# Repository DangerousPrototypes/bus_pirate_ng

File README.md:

# bus_pirate_ng
Bus Pirate NG firmware and hardware

Check the blog at http://dangerousprototypes.com/blog/2018/09/13/prototype-bus-pirate-next-gen-v1/<br><br>
---
### Building
- Install toolchain:
```
sudo apt-get update -y
sudo apt-get install -y gcc-arm-none-eabi
```
- Clone repository:
```
git clone --recursive https://github.com/DangerousPrototypes/bus_pirate_ng
cd bus_pirate_ng
```
- Compile modules in this order:
```
make -C libopencm3 lib/stm32/f1
make -C bootloader images
```
- Compile Bus Pirate:
```
make -C source images
```
- Output images:
```
bootloader/usbdfu.bin
source/buspirateNG.bin
```
<br>

---
### Bootloader
The firmware is compiled expecting a bootloader offset of 0x2000.<br>
The generated BusPirate image doesn't contain the bootloader, if your stm32 doesn't have it you must first flash:
```
bootloader/usbdfu.bin
```
Then enter DFU mode and flash:
```
source/buspirateNG.bin
```
### Bootloader-less
You can skip the bootloader entirely by modifying [`source/buspirateNG.ld`](source/buspirateNG.ld#L23),<br>
Replace:
```
ORIGIN = 0x08002000, LENGTH = 120K
```
With:
```
ORIGIN = 0x08000000, LENGTH = 128K
```
Now simply flash ```source/buspirateNG.bin``` into the stm32 using your favourite programmer.<br>

---
### Pinout
Pin functions are described at [`source/platform/beta2.h`](source/platform/beta2.h).
<br>

---
### Basic functionality using a BluePill
You can use this firmware in a simple Bluepill, skipping all the extra circuitry, but requires tweaking to ignore the PSU check.<br>
Edit ```initUI``` function at [`source/UI.c`](source/UI.c#L167) and change:
```
modeConfig.psu=0;
```
To:
```
modeConfig.psu=1;
```
Don't use PSU commands (w/W) after this modification!<br>
Keep in mind the bare STM32 can only talk 3.3V in push-pull mode and 5V in open-drain mode!<br>

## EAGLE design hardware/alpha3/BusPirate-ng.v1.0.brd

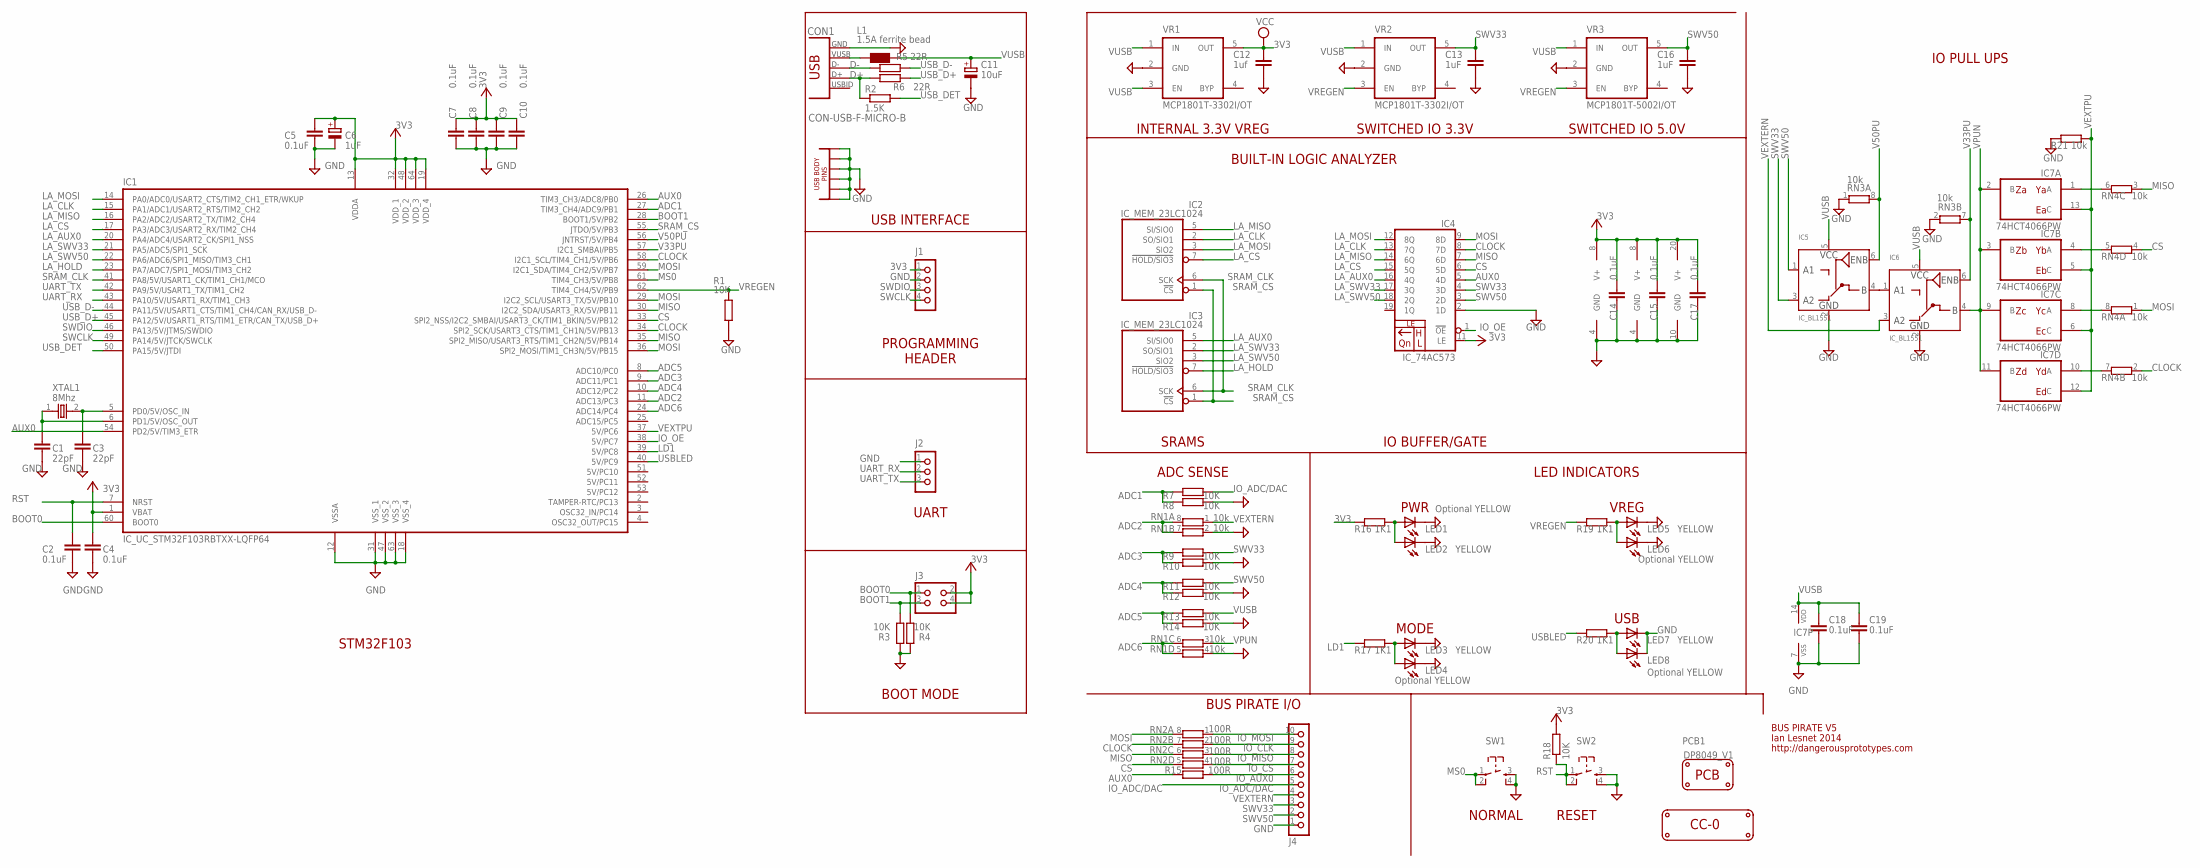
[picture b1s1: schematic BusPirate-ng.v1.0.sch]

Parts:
C1, C3: 22pF; C0603
C2, C4, C5, C7, C8, C9, C10, C14, C15, C17, C18, C19: 0.1uF; C0603
C6: 1uF; SMC_A
C11: 10uF; SMC_A
C12: 1uf; C0603
C13, C16: 1uF; C0603
CON1: CON-USB-F-MICRO-B; CON_USB_MICRO-B-1-MD05SMXXX-01
IC1: IC_UC_STM32F103RBTXX-LQFP64; LQFP64
IC2, IC3: IC_MEM_23LC1024; SOIC-8
IC4: IC_74AC573; TSSOP-20
IC5, IC6: IC_BL1551; SOT-363
IC7: 74HCT4066PW; 40XX_TSSOP14
J1: CON_HEADER_1X04; M1X4
J2: CON_HEADER_1X03-PTH; M1X3
J3: CON_HEADER_2X02-PTH; M2X2
J4: CON_HEADER_1X10-RIGHT_ANGLED_PTH_SHROUDED; M1X10_MALE_RIGHT_ANGLES_PTH_SHROUDED
L1: 1.5A ferrite bead; WE-KI_0805_B
LED1, LED4, LED6, LED8: Optional YELLOW; LED-805
LED2, LED3, LED5, LED7: YELLOW; LED-805
LOGO1: LOGO_CC-0
PCB1: PCB_DP_RECTANGLE-80X49; DP8049_V1
R1, R18: 10K; R603
R2: 1.5K; R603
R3, R4, R7, R8, R9, R10, R11, R12, R13, R14: 10K; R0603
R5, R6: 22R; R603
R15: 100R; R603
R16, R17, R19, R20: 1K1; R603
R21: 10k; R603
RN1, RN3, RN4: 10k; RN8P-4R-CRA06S
RN2: 100R; RN8P-4R-CRA06S
SW1, SW2: SW_TACT_4P; SW_TACT_SMALL
VR1, VR2: MCP1801T-3302I/OT; SOT-23-5@1
VR3: MCP1801T-5002I/OT; SOT-23-5@1
XTAL1: 8Mhz; XTAL_4X6

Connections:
3V3: C4.2, C5.2, C6.+, C7.2, C8.2, C9.2, C10.2, C12.1, C14.1, C15.1, C17.1, IC1.1 (VBAT), IC1.13 (VDDA), IC1.19 (VDD_4), IC1.32 (VDD_1), IC1.48 (VDD_2), IC1.64 (VDD_3), IC2.8 (V+), IC3.8 (V+), IC4.11 (LE), IC4.20 (V+), J1.1, J3.2, J3.4, R16.2, R18.2, VR1.5 (OUT)
ADC1: IC1.27 (TIM3_CH4/ADC9/PB1), R7.2, R8.2
ADC2: IC1.11 (ADC13/PC3), RN1.7 (2), RN1.8 (2)
ADC3: IC1.9 (ADC11/PC1), R9.2, R10.2
ADC4: IC1.10 (ADC12/PC2), R11.2, R12.2
ADC5: IC1.8 (ADC10/PC0), R13.2, R14.2
ADC6: IC1.24 (ADC14/PC4), RN1.5 (2), RN1.6 (2)
AUX0: IC1.26 (TIM3_CH3/ADC8/PB0), IC1.54 (PD2/5V/TIM3_ETR), IC4.5 (4D), R15.1
BOOT0: IC1.60 (BOOT0), J3.1, R4.1
BOOT1: IC1.28 (BOOT1/5V/PB2), J3.3, R3.1
CLOCK: IC1.34 (SPI2_SCK/USART3_CTS/TIM1_CH1N/5V/PB13), IC1.58 (I2C1_SCL/TIM4_CH1/5V/PB6), IC4.8 (7D), RN2.7 (2), RN4.2 (1)
CS: IC1.33 (SPI2_NSS/I2C2_SMBAI/USART3_CK/TIM1_BKIN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), IC4.6 (5D), RN2.5 (2), RN4.4 (1)
D+: CON1.P3 (D+), R2.1, R6.2
D-: CON1.P2 (D-), R5.2
EXVUSB: CON1.P1 (VUSB), L1.2 (1)
GND: C1.1, C2.1, C3.1, C4.1, C5.1, C6.-, C7.1, C8.1, C9.1, C10.1, C11.-, C12.2, C13.2, C14.2, C15.2, C16.2, C17.2, C18.2, C19.2, CON1.GND1, CON1.GND2, CON1.GND3, CON1.GND4, CON1.GND5, CON1.GND6, CON1.P5 (GND), IC1.12 (VSSA), IC1.18 (VSS_4), IC1.31 (VSS_1), IC1.47 (VSS_2), IC1.63 (VSS_3), IC2.4 (GND), IC3.4 (GND), IC4.2 (1D), IC4.10 (GND), IC5.2 (GND), IC6.2 (GND), IC7.7 (VSS), J1.2, J2.1, J4.1, LED1.C, LED2.C, LED3.C, LED4.C, LED5.C, LED6.C, LED7.C, LED8.C, R1.2, R3.2, R4.2, R8.1, R10.1, R12.1, R14.1, R21.2, RN1.2 (1), RN1.4 (1), RN3.1, RN3.2 (1), SW1.3, SW1.4, SW2.3, SW2.4, VR1.2 (GND), VR2.2 (GND), VR3.2 (GND)
IO_ADC/DAC: J4.5, R7.1
IO_AUX0: J4.6, R15.2
IO_CLK: J4.9, RN2.2 (1)
IO_CS: J4.7, RN2.4 (1)
IO_MISO: J4.8, RN2.3 (1)
IO_MOSI: J4.10, RN2.1
IO_OE: IC1.38 (5V/PC7), IC4.1 (!OE)
LA_AUX0: IC1.20 (PA4/ADC4/USART2_CK/SPI1_NSS), IC3.5 (SI/SIO0), IC4.16 (4Q)
LA_CLK: IC1.15 (PA1/ADC1/USART2_RTS/TIM2_CH2), IC2.2 (SO/SIO1), IC4.13 (7Q)
LA_CS: IC1.17 (PA3/ADC3/USART2_RX/TIM2_CH4), IC2.7 (!HOLD/SIO3), IC4.15 (5Q)
LA_HOLD: IC1.23 (PA7/ADC7/SPI1_MOSI/TIM3_CH2), IC3.7 (!HOLD/SIO3)
LA_MISO: IC1.16 (PA2/ADC2/USART2_TX/TIM2_CH4), IC2.5 (SI/SIO0), IC4.14 (6Q)
LA_MOSI: IC1.14 (PA0/ADC0/USART2_CTS/TIM2_CH1_ETR/WKUP), IC2.3 (SIO2), IC4.12 (8Q)
LA_SWV33: IC1.21 (PA5/ADC5/SPI1_SCK), IC3.2 (SO/SIO1), IC4.17 (3Q)
LA_SWV50: IC1.22 (PA6/ADC6/SPI1_MISO/TIM3_CH1), IC3.3 (SIO2), IC4.18 (2Q)
LD1: IC1.39 (5V/PC8), R17.2
MISO: IC1.30 (I2C2_SDA/USART3_RX/5V/PB11), IC1.35 (SPI2_MISO/USART3_RTS/TIM1_CH2N/5V/PB14), IC4.7 (6D), RN2.6 (2), RN4.3 (1)
MOSI: IC1.29 (I2C2_SCL/USART3_TX/5V/PB10), IC1.36 (SPI2_MOSI/TIM1_CH3N/5V/PB15), IC1.59 (I2C1_SDA/TIM4_CH2/5V/PB7), IC4.9 (8D), RN2.8 (2), RN4.1
MS0: IC1.61 (TIM4_CH3/5V/PB8), SW1.1, SW1.2
unnamed: IC5.4 (B), IC6.1 (A1)
unnamed: IC7.1 (A), RN4.6 (2)
unnamed: IC7.4 (A), RN4.5 (2)
unnamed: IC7.8 (A), RN4.8 (2)
unnamed: IC7.10 (A), RN4.7 (2)
unnamed: LED3.A, LED4.A, R17.1
unnamed: LED1.A, LED2.A, R16.1
unnamed: LED7.A, LED8.A, R20.1
unnamed: C3.2, IC1.5 (PD0/5V/OSC_IN), XTAL1.2
unnamed: LED5.A, LED6.A, R19.1
unnamed: C1.2, IC1.6 (PD1/5V/OSC_OUT), XTAL1.1
RST: C2.2, IC1.7 (NRST), R18.1, SW2.1, SW2.2
SRAM_CLK: IC1.41 (PA8/5V/USART1_CK/TIM1_CH1/MCO), IC2.6 (SCK), IC3.6 (SCK)
SRAM_CS: IC1.55 (JTDO/5V/PB3), IC2.1 (!CS), IC3.1 (!CS)
SWCLK: IC1.49 (PA14/5V/JTCK/SWCLK), J1.4
SWDIO: IC1.46 (PA13/5V/JTMS/SWDIO), J1.3
SWV33: C13.1, IC4.4 (3D), IC5.3 (A2), J4.3, R9.1, VR2.5 (OUT)
SWV50: C16.1, IC4.3 (2D), IC5.1 (A1), J4.2, R11.1, VR3.5 (OUT)
UART_RX: IC1.43 (PA10/5V/USART1_RX/TIM1_CH3), J2.2
UART_TX: IC1.42 (PA9/5V/USART1_TX/TIM1_CH2), J2.3
USBLED: IC1.40 (5V/PC9), R20.2
USB_D+: IC1.45 (PA12/5V/USART1_RTS/TIM1_ETR/CAN_TX/USB_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), R6.1
USB_D-: IC1.44 (PA11/5V/USART1_CTS/TIM1_CH4/CAN_RX/USB_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), R5.1
USB_DET: IC1.50 (PA15/5V/JTDI), R2.2
V33PU: IC1.57 (I2C1_SMBAI/PB5), IC6.6 (ENB), RN3.7 (2)
V50PU: IC1.56 (JNTRST/5V/PB4), IC5.6 (ENB), RN3.8 (2)
VEXTERN: IC6.3 (A2), J4.4, RN1.1
VEXTPU: IC1.37 (5V/PC6), IC7.5 (C), IC7.6 (C), IC7.12 (C), IC7.13 (C), R21.1
VPUN: IC6.4 (B), IC7.2 (B), IC7.3 (B), IC7.9 (B), IC7.11 (B), RN1.3 (1)
VREGEN: IC1.62 (TIM4_CH4/5V/PB9), R1.1, R19.2, VR2.3 (EN), VR3.3 (EN)
VUSB: C11.+, C18.1, C19.1, IC5.5 (VCC), IC6.5 (VCC), IC7.14 (VDD), L1.1 (2), R13.1, VR1.1 (IN), VR1.3 (EN), VR2.1 (IN), VR3.1 (IN)

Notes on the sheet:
BUS PIRATE V5
Ian Lesnet 2014
http://dangerousprototypes.com
SRAMS
IO BUFFER/GATE
BUS PIRATE I/O
BOOT MODE
PWR
MODE
VREG
PROGRAMMING HEADER
USB
INTERNAL 3.3V VREG
SWITCHED IO 3.3V
SWITCHED IO 5.0V
BUILT-IN LOGIC ANALYZER
ADC SENSE
USB INTERFACE
STM32F103
NORMAL
RESET
IO PULL UPS
LED INDICATORS
UART

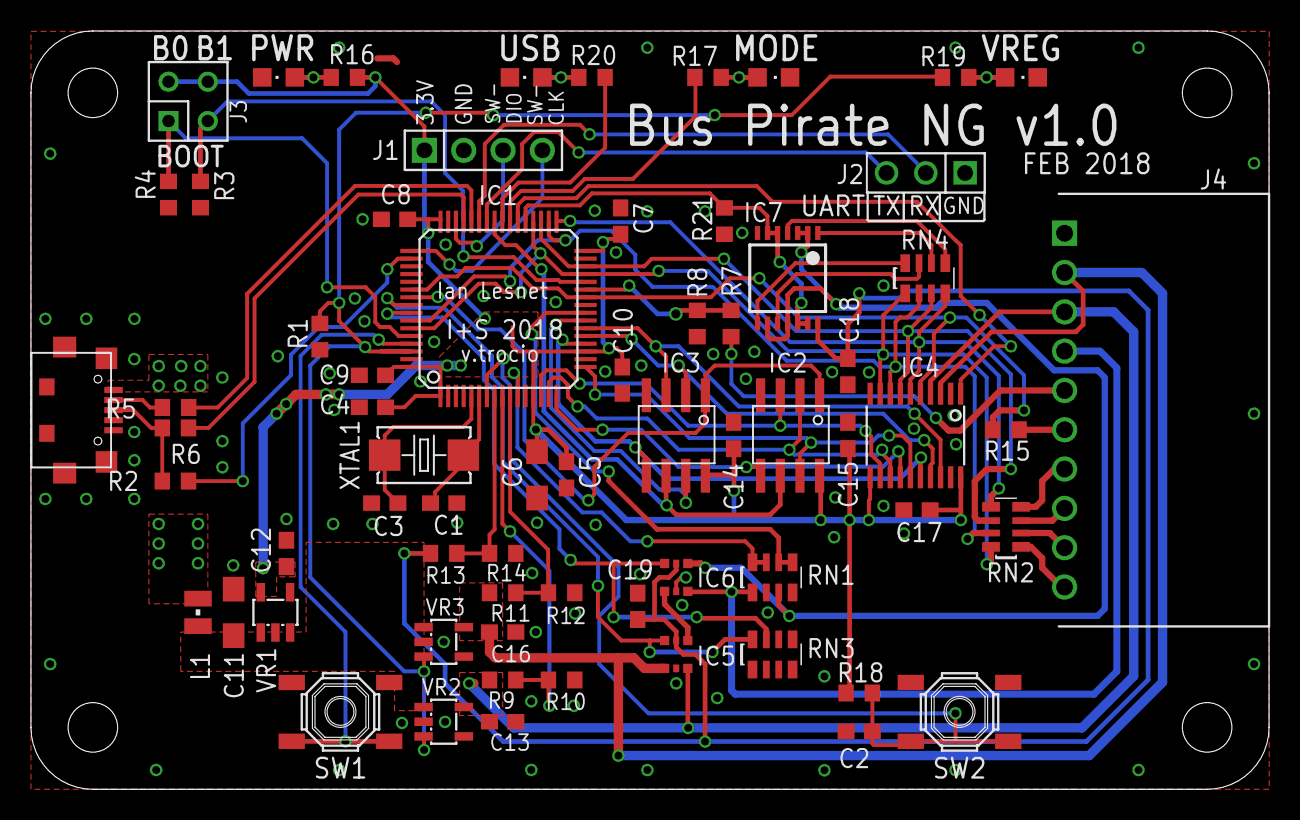
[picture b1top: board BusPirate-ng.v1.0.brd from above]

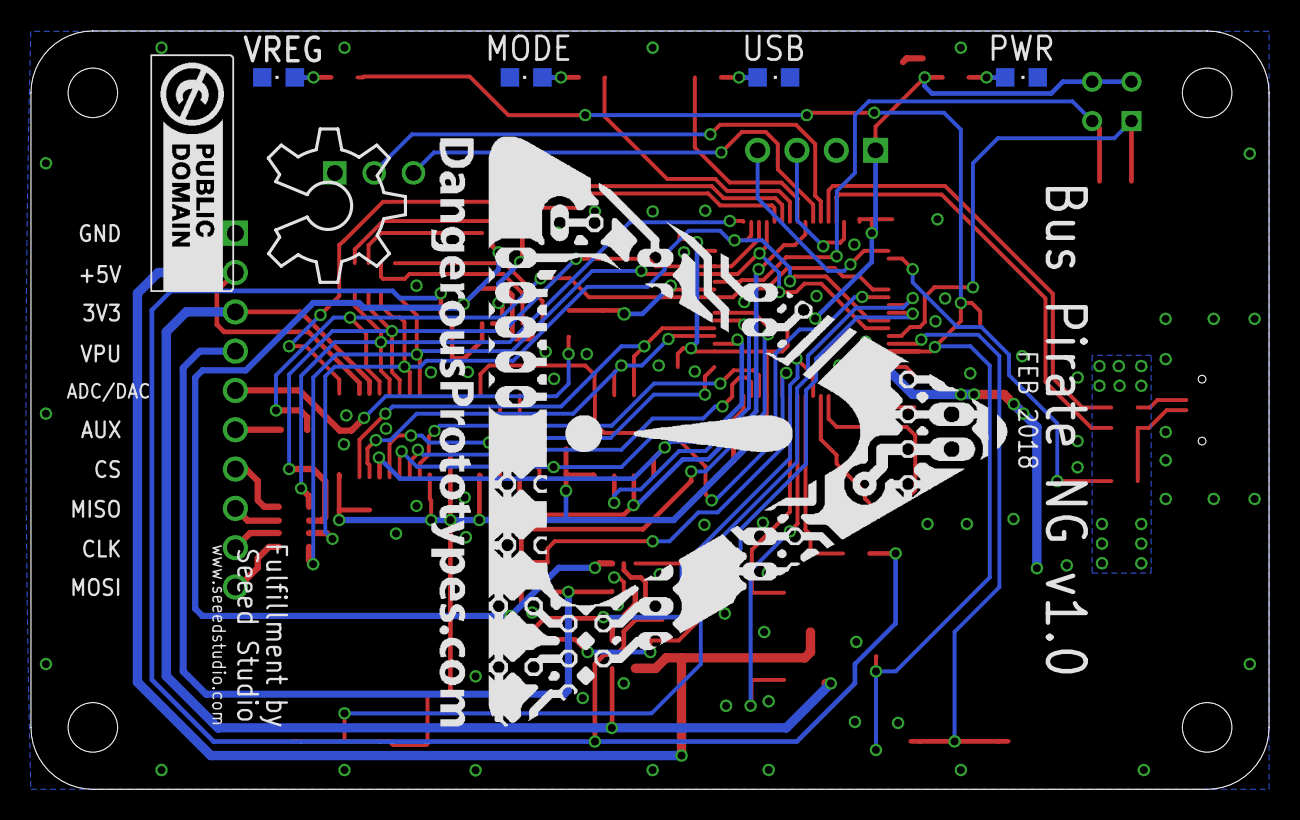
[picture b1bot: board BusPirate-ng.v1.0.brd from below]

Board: 2 copper layers, 80.0 x 49.0 mm, 76 parts (7 on the bottom side), 66 nets.

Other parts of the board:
U$1: DP-LOGO
U$2: OSHW_8X350_NOTEXT
U$4: DP_LOGO_ART_1.5X1.5

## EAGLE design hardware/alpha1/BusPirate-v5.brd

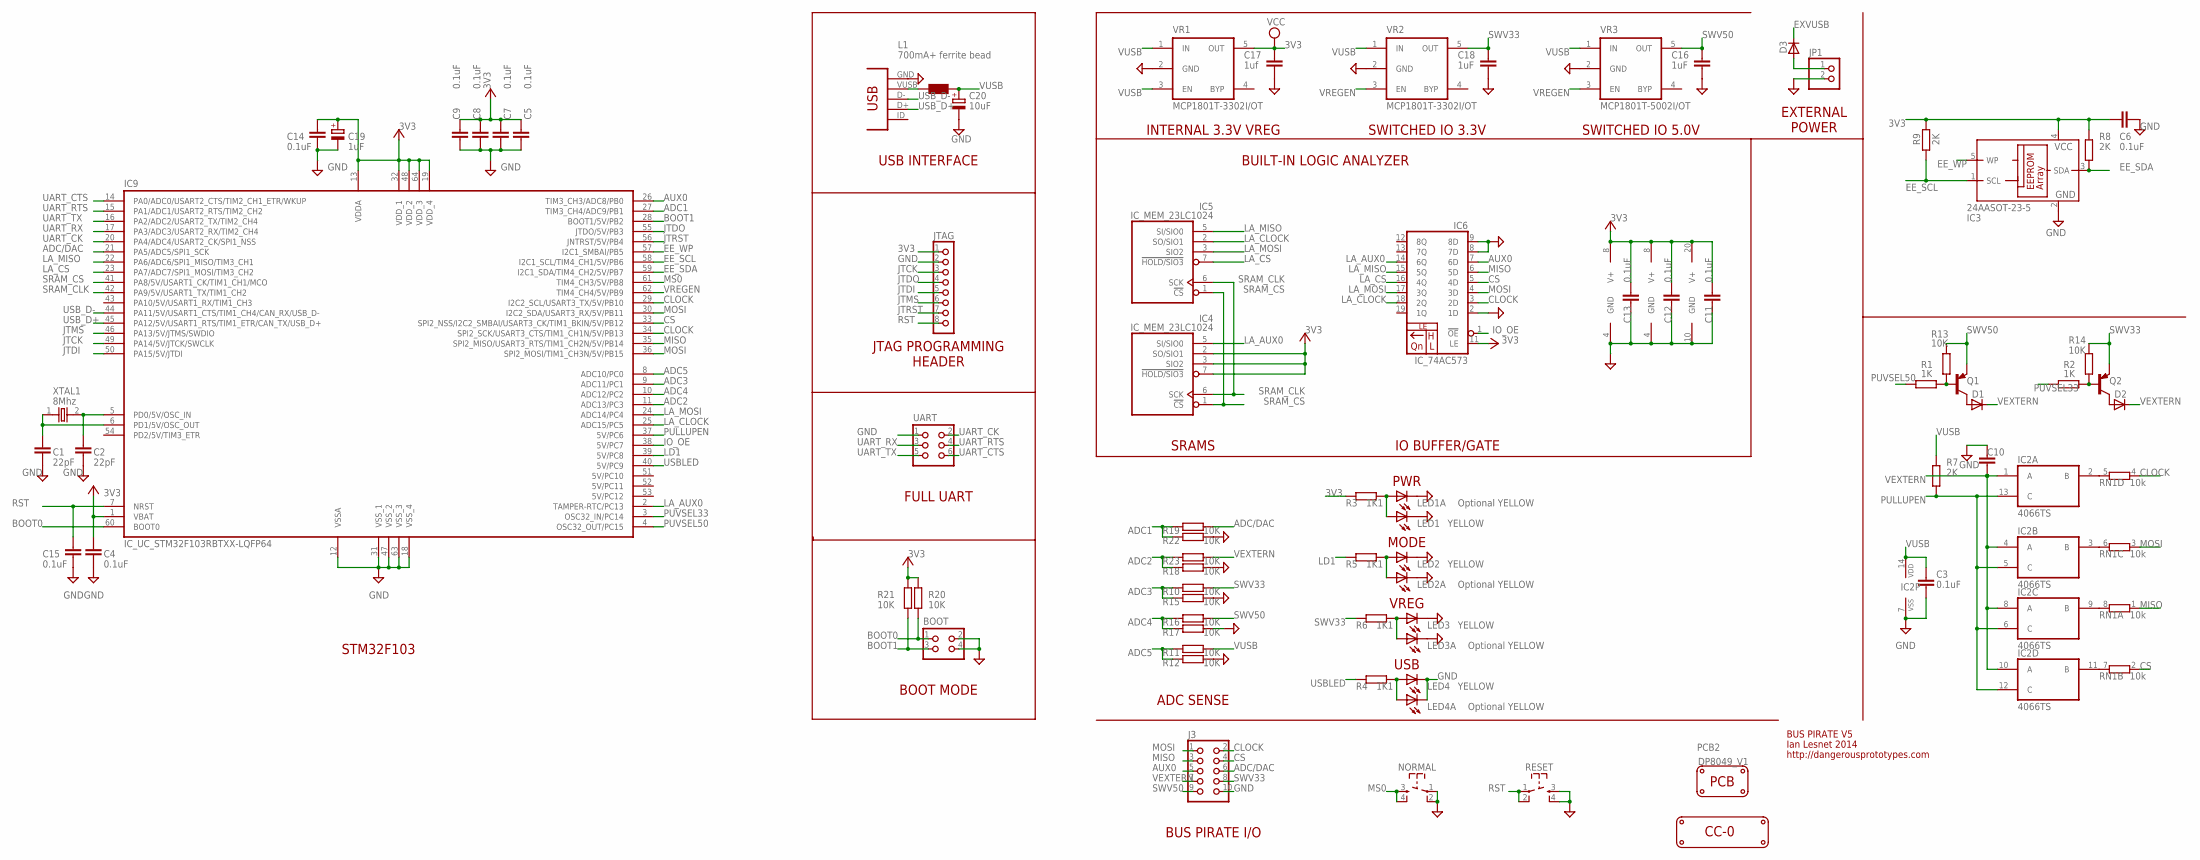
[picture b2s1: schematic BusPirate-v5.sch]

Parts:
BOOT: CON_HEADER_2X02-PTH; M2X2
C1, C2: 22pF; C0603
C3, C4, C5, C6, C7, C8, C9, C10, C11, C12, C13, C14, C15: 0.1uF; C0603
C16, C18: 1uF; C0603
C17: 1uf; C0603
C19: 1uF; SMC_A
C20: 10uF; SMC_A
D1, D2, D3: MBR0520LT; SOD123
IC2: 4066TS; 40XX_TSSOP14
IC3: 24AASOT-23-5; SOT-23-5@1
IC4, IC5: IC_MEM_23LC1024; SOIC-8
IC6: IC_74AC573; TSSOP-20
IC9: IC_UC_STM32F103RBTXX-LQFP64; LQFP64
J3: CON_HEADER_2X05-PTH+SHROUDED_A; PINSHRD_PTH_2X05
JP1: PINHD-1X02_2.54-S; 1X02-S
JTAG: CON_HEADER_1X08-PTH; M1X8
L1: 700mA+ ferrite bead; WE-KI_0805_B
LED1, LED2, LED3, LED4: YELLOW; LED-603
LED1A, LED2A, LED3A, LED4A: Optional YELLOW; LED-603
LOGO1: LOGO_CC-0
NORMAL: SW_TACT_4P; SW_TACT_SMALL
PCB2: PCB_DP_RECTANGLE-80X49; DP8049_V1
Q1, Q2: MMBTA56-SOT23; SOT23
R1, R2: 1K; R0603
R3, R4, R5, R6: 1K1; R603
R7, R8, R9: 2K; R0603
R10, R11, R12, R14, R15, R16, R17, R18, R19, R20, R21, R22, R23: 10K; R0603
R13: 10K; R603
RESET: SW_TACT_4P; SW_TACT_SMALL
RN1: 10k; RN8P-4R-CRA06S
UART: CON_HEADER_2X03-PTH; M2X3
USB: USB mini-b; CONN_USB_MINI-B
VR1, VR2: MCP1801T-3302I/OT; SOT-23-5@1
VR3: MCP1801T-5002I/OT; SOT-23-5@1
XTAL1: 8Mhz; XTAL_4X6

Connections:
3V3: C4.2, C5.2, C6.1, C7.2, C8.2, C9.2, C11.1, C12.1, C13.1, C14.2, C17.1, C19.+, IC3.4 (VCC), IC4.2 (SO/SIO1), IC4.3 (SIO2), IC4.7 (!HOLD/SIO3), IC4.8 (V+), IC5.8 (V+), IC6.11 (LE), IC6.20 (V+), IC9.1 (VBAT), IC9.13 (VDDA), IC9.19 (VDD_4), IC9.32 (VDD_1), IC9.48 (VDD_2), IC9.64 (VDD_3), JTAG.1, R3.2, R8.2, R9.2, R20.2, R21.2, VR1.5 (OUT)
ADC1: IC9.27 (TIM3_CH4/ADC9/PB1), R19.2, R22.2
ADC2: IC9.11 (ADC13/PC3), R18.2, R23.2
ADC3: IC9.9 (ADC11/PC1), R10.2, R15.2
ADC4: IC9.10 (ADC12/PC2), R16.2, R17.2
ADC5: IC9.8 (ADC10/PC0), R11.2, R12.2
ADC/DAC: IC9.21 (PA5/ADC5/SPI1_SCK), J3.6, R19.1
AUX0: IC6.7 (6D), IC9.26 (TIM3_CH3/ADC8/PB0), J3.5
BOOT0: BOOT.1, IC9.60 (BOOT0), R20.1
BOOT1: BOOT.3, IC9.28 (BOOT1/5V/PB2), R21.1
CLOCK: IC6.3 (2D), IC9.29 (I2C2_SCL/USART3_TX/5V/PB10), IC9.34 (SPI2_SCK/USART3_CTS/TIM1_CH1N/5V/PB13), J3.2, RN1.4 (1)
CS: IC6.5 (4D), IC9.33 (SPI2_NSS/I2C2_SMBAI/USART3_CK/TIM1_BKIN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), J3.4, RN1.2 (1)
EE_SCL: IC3.1 (SCL), IC9.58 (I2C1_SCL/TIM4_CH1/5V/PB6), R9.1
EE_SDA: IC3.3 (SDA), IC9.59 (I2C1_SDA/TIM4_CH2/5V/PB7), R8.1
EE_WP: IC3.5 (WP), IC9.57 (I2C1_SMBAI/PB5)
EXVUSB: D3.C, L1.2 (1), USB.VUSB
GND: BOOT.2, BOOT.4, C1.1, C2.1, C3.2, C4.1, C5.1, C6.2, C7.1, C8.1, C9.1, C10.2, C11.2, C12.2, C13.2, C14.1, C15.1, C16.2, C17.2, C18.2, C19.-, C20.-, IC2.7 (VSS), IC3.2 (GND), IC4.4 (GND), IC5.4 (GND), IC6.2 (1D), IC6.8 (7D), IC6.9 (8D), IC6.10 (GND), IC9.12 (VSSA), IC9.18 (VSS_4), IC9.31 (VSS_1), IC9.47 (VSS_2), IC9.63 (VSS_3), J3.10, JP1.2, JTAG.2, LED1.C, LED1A.C, LED2.C, LED2A.C, LED3.C, LED3A.C, LED4.C, LED4A.C, NORMAL.1, NORMAL.2, R12.1, R15.1, R17.1, R18.1, R22.1, RESET.3, RESET.4, UART.1, USB.GND, VR1.2 (GND), VR2.2 (GND), VR3.2 (GND)
IO_OE: IC6.1 (!OE), IC9.38 (5V/PC7)
JTCK: IC9.49 (PA14/5V/JTCK/SWCLK), JTAG.3
JTDI: IC9.50 (PA15/5V/JTDI), JTAG.5
JTDO: IC9.55 (JTDO/5V/PB3), JTAG.4
JTMS: IC9.46 (PA13/5V/JTMS/SWDIO), JTAG.6
JTRST: IC9.56 (JNTRST/5V/PB4), JTAG.7
LA_AUX0: IC4.5 (SI/SIO0), IC6.14 (6Q), IC9.2 (TAMPER-RTC/PC13)
LA_CLOCK: IC5.2 (SO/SIO1), IC6.18 (2Q), IC9.25 (ADC15/PC5)
LA_CS: IC5.7 (!HOLD/SIO3), IC6.16 (4Q), IC9.23 (PA7/ADC7/SPI1_MOSI/TIM3_CH2)
LA_MISO: IC5.5 (SI/SIO0), IC6.15 (5Q), IC9.22 (PA6/ADC6/SPI1_MISO/TIM3_CH1)
LA_MOSI: IC5.3 (SIO2), IC6.17 (3Q), IC9.24 (ADC14/PC4)
LD1: IC9.39 (5V/PC8), R5.2
MISO: IC6.6 (5D), IC9.35 (SPI2_MISO/USART3_RTS/TIM1_CH2N/5V/PB14), J3.3, RN1.1
MOSI: IC6.4 (3D), IC9.30 (I2C2_SDA/USART3_RX/5V/PB11), IC9.36 (SPI2_MOSI/TIM1_CH3N/5V/PB15), J3.1, RN1.3 (1)
MS0: IC9.61 (TIM4_CH3/5V/PB8), NORMAL.3, NORMAL.4
unnamed: IC2.2 (B), RN1.5 (2)
unnamed: IC2.11 (B), RN1.7 (2)
unnamed: D1.A, Q1.3 (C)
unnamed: IC2.9 (B), RN1.8 (2)
unnamed: IC2.3 (B), RN1.6 (2)
unnamed: LED2.A, LED2A.A, R5.1
unnamed: LED1.A, LED1A.A, R3.1
unnamed: Q2.1 (B), R2.1, R14.2
unnamed: LED4.A, LED4A.A, R4.1
unnamed: D2.A, Q2.3 (C)
unnamed: D3.A, JP1.1
unnamed: C2.2, IC9.5 (PD0/5V/OSC_IN), XTAL1.2
unnamed: Q1.1 (B), R1.1, R13.2
unnamed: LED3.A, LED3A.A, R6.1
unnamed: C1.2, IC9.6 (PD1/5V/OSC_OUT), XTAL1.1
PULLUPEN: IC2.5 (C), IC2.6 (C), IC2.12 (C), IC2.13 (C), IC9.37 (5V/PC6), R7.2
PUVSEL33: IC9.3 (OSC32_IN/PC14), R2.2
PUVSEL50: IC9.4 (OSC32_OUT/PC15), R1.2
RST: C15.2, IC9.7 (NRST), JTAG.8, RESET.1, RESET.2
SRAM_CLK: IC4.6 (SCK), IC5.6 (SCK), IC9.42 (PA9/5V/USART1_TX/TIM1_CH2)
SRAM_CS: IC4.1 (!CS), IC5.1 (!CS), IC9.41 (PA8/5V/USART1_CK/TIM1_CH1/MCO)
SWV33: C18.1, J3.8, Q2.2 (E), R6.2, R10.1, R14.1, VR2.5 (OUT)
SWV50: C16.1, J3.9, Q1.2 (E), R13.1, R16.1, VR3.5 (OUT)
UART_CK: IC9.20 (PA4/ADC4/USART2_CK/SPI1_NSS), UART.2
UART_CTS: IC9.14 (PA0/ADC0/USART2_CTS/TIM2_CH1_ETR/WKUP), UART.6
UART_RTS: IC9.15 (PA1/ADC1/USART2_RTS/TIM2_CH2), UART.4
UART_RX: IC9.17 (PA3/ADC3/USART2_RX/TIM2_CH4), UART.3
UART_TX: IC9.16 (PA2/ADC2/USART2_TX/TIM2_CH4), UART.5
USBLED: IC9.40 (5V/PC9), R4.2
USB_D+: IC9.45 (PA12/5V/USART1_RTS/TIM1_ETR/CAN_TX/USB_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), USB.D+
USB_D-: IC9.44 (PA11/5V/USART1_CTS/TIM1_CH4/CAN_RX/USB_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), USB.D-
VEXTERN: C10.1, D1.C, D2.C, IC2.1 (A), IC2.4 (A), IC2.8 (A), IC2.10 (A), J3.7, R23.1
VREGEN: IC9.62 (TIM4_CH4/5V/PB9), VR2.3 (EN), VR3.3 (EN)
VUSB: C3.1, C20.+, IC2.14 (VDD), L1.1 (2), R7.1, R11.1, VR1.1 (IN), VR1.3 (EN), VR2.1 (IN), VR3.1 (IN)

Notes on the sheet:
BUS PIRATE V5
Ian Lesnet 2014
http://dangerousprototypes.com
SRAMS
IO BUFFER/GATE
FULL UART
BUS PIRATE I/O
BOOT MODE
PWR
MODE
VREG
JTAG PROGRAMMING HEADER
USB
INTERNAL 3.3V VREG
SWITCHED IO 3.3V
SWITCHED IO 5.0V
BUILT-IN LOGIC ANALYZER
ADC SENSE
USB INTERFACE
STM32F103
EXTERNAL POWER

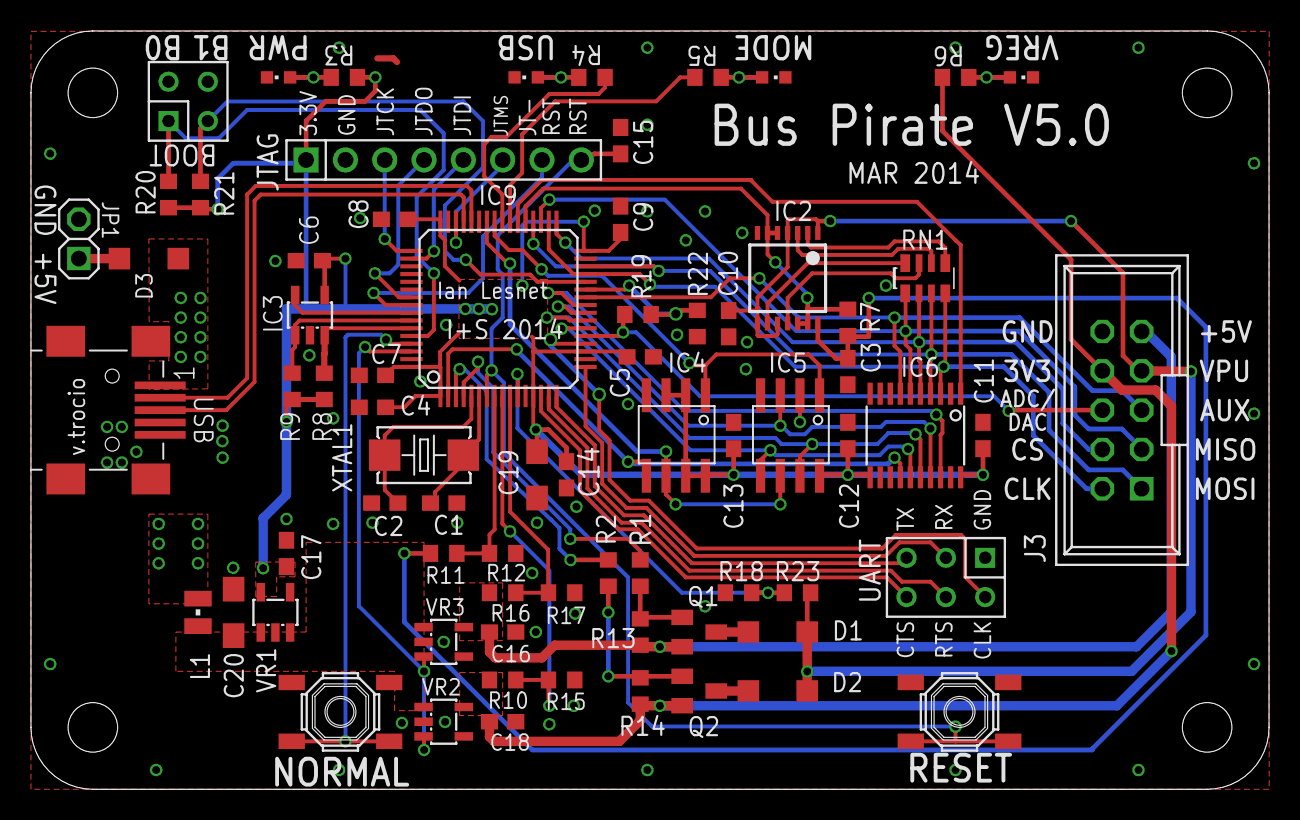
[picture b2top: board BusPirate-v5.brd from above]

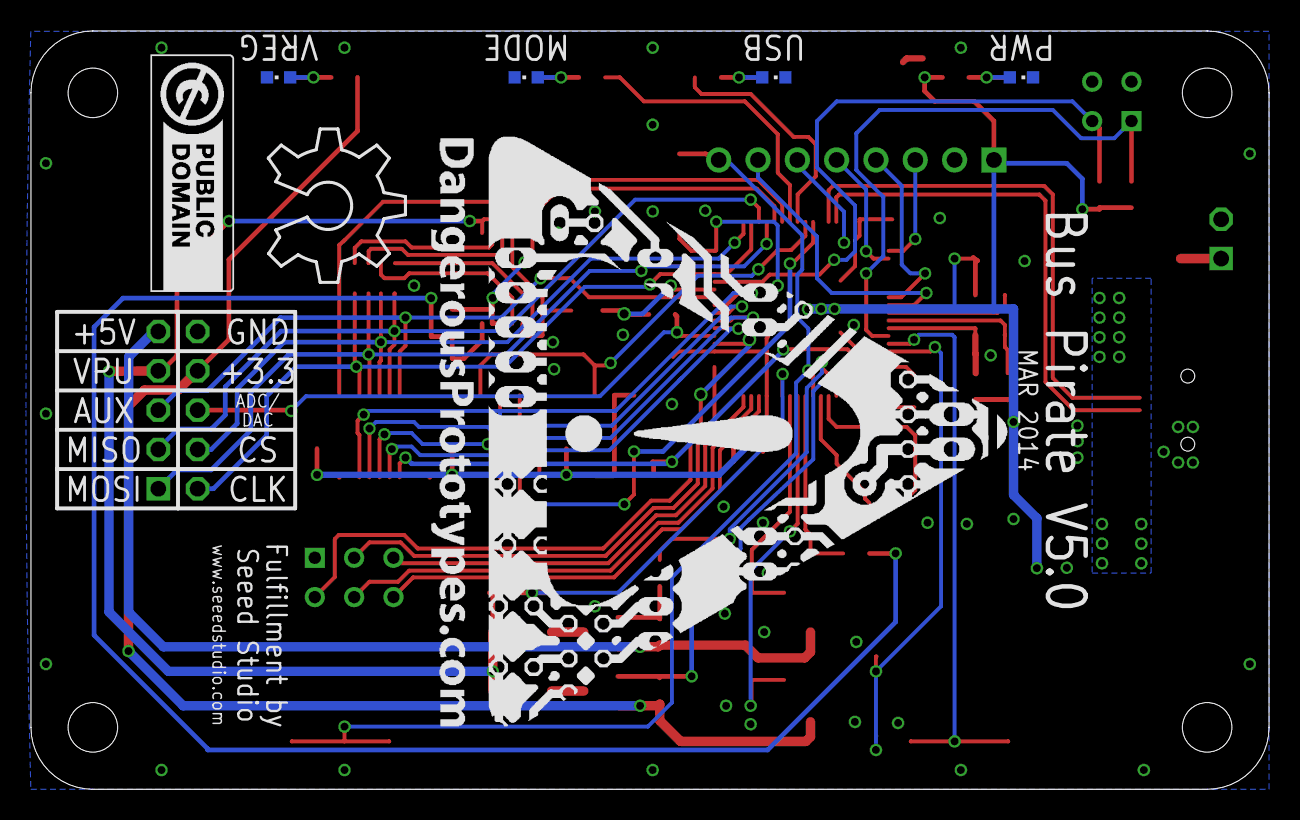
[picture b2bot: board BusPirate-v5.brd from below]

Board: 2 copper layers, 80.0 x 49.0 mm, 80 parts (7 on the bottom side), 66 nets.

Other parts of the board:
U$2: OSHW_8X350_NOTEXT
U$4: DP_LOGO_ART_1.5X1.5

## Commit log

2017-11-29 added morecore commands and SPI protocol
2017-11-29 removed usb vid/pid
2017-12-01 Added more functionality to the coreframework
2017-12-04 Added more core functions
2017-12-06 add UART and improved core
2017-12-10 added userstorage, added more corecommands
2017-12-14 added pullup commands
2017-12-19 added I2C protocol
2017-12-20 renamed AUX.c because some clients cant handle this
2017-12-20 bus pirate ng licenses and boards for USB VID/PID approval
2017-12-20 update license to GPL 3.0 for compatibility with libopencms3. Will dual license our code and hardware CC-0 later when we figure out how to do that!
2017-12-20 fixed error in integer parser and fixed i2c read (for now)
2017-12-21 Added PWM function to core
2017-12-28 - added frequency measurement/count - add binary to output - tweaked the '=' command
2017-12-29 - fixed a bug in getint() - added macro handler - some preliminary logic analyzer code
2018-01-01 - added ANSI codes for colors/textstyles - added send string - implemented the bitorder switch
2018-01-09 - added software 3wire (SPI like) - minor UI tweaks - cleaned up protocols - removed some visual debugging
2018-01-17 - removed lots of 'debugging' from the protocols - fixed HWSPI - removed unused commands from the protocols
2018-01-17 - fixed naming in SPI
2018-01-18 - added software 2 wire (I2C like) - add comments
2018-01-23 - cleaned up code - renamed defines in platform (better readable) - add protocol specific help (only I2C for now)
2018-01-24 added protocol help for SPI, USART, software 3 wire
2018-01-26 - added periodic function to protocols - determine the mode of the pin (i menu)
2018-02-08 - added support for first beta HW (platform/beta1.h - added support for mode, usb LEDs - usb pullup is configurable - fixed bugs in sw3w: now sets states of CS and CLK correctly - fixed bugs in hwuas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
2018-02-21 initial logic analyzer code. WIP/not working yet
2018-02-26 LA byte test
2018-02-26 Updates and test of Logic analyzer 1 and 4 bit read and write modes. Try macro 4. both seem to be working.
2018-02-26 - added DFU bootloader - added #, $ as command (jump into bootloade/reset)
2018-03-02 -fixed logic analyzer -fixed bug in userinput
2018-03-07 added extra CDC endpoint
2018-03-07 added proper serial number to usbdescriptor
2018-03-14 - change software to new hardware (feb 2017)
2018-03-16 - fixed LA
2018-03-17 manual logic analyzer test
2018-03-19 open latch to probe sram pins
2018-03-20 add spi la changes
2018-03-21 - command line can now be editted - cleaned up bootloader folder
2018-03-22 - added cmd history (arrow up/down)
2018-03-23 Logic analyzer updates
2018-03-23 fixed unused variable
2018-03-23 Revert "fixed unused variable"
    This reverts commit 46a14085b95fabf4c57e2ae5b59cb056e28aa3ca.
2018-03-23 - fixed lockup in commandline - fixed 'randomly' sent NULL chars
2018-03-23 Revert "Revert "fixed unused variable""
    This reverts commit 1c3654b1548de7b261ad4106a16f7bc4517599f1.
2018-03-24 Logic analyzer current progress. Reverted change in cdcacm that was causing freezing
2018-03-27 - finally (?) fixed NULL bug in cdcacm - added direct io mode
2018-03-28 LA calculate period and apply from mode
2018-03-28 added LCD(SPI) mode; just HD44780 is available yet
2018-03-29 Pass logic analyzer period through modeconfig struct
2018-03-29 add logic analyzer to various modes. send null samples when reach end of data in large capture request for live captures
2018-03-29 Fix variable names
2018-04-01 Logic analyzer user mode working. Partial implementation of SUMP standalone mode.
2018-04-03 switched to interrupts for usb communication
2018-04-03 added buffercheck for second cdc channel
2018-04-05 white space change for testing
2018-04-05 white space change
2018-04-06 induce warning and error
2018-04-06 removed induced error
2018-04-06 removed induced warn
2018-04-10 - finally fixed cdc (?) - cosmetic changes to function names
2018-04-12 - added 1 wire protocol (not working atm) - added place holder for I2C LCD protocol
2018-04-16 - added a timer for proper delays - fixed 1 wire - added device list to 1wire from http://owfs.sourceforge.net/simple_family.html
2018-04-18 - added ST7735D/R to LCD protocol
2018-04-19 - renamed ST7735R to ST7735 as it support D and R versions - added subprotocolname to commandline - added menu to LCD library to choose which display is being probed - minor UI tweaks
2018-04-23 - added timeout to I2C - added short/no pullup check to I2C - added address search macro to I2C
2018-04-26 Updated UI strings
2018-04-26 updated to match previous versions: order of protocols, protocol names, conditional include of protocol header files
2018-04-26 - HW init is now done just before the first command that interacts on the bus; this will allow to properly setup the powersupplies before interacting - fixed bug in pinstate display
2018-04-27 SWI2C first push, uncompiled/tested
2018-04-27 update make file, update defines to remove compile errors
2018-04-27 Fixed all compile errors in SWI2C. Moved all gpio_ calls to macros in .h
2018-04-28 rework SW2W to use macros. rework SWI2C to reuse SW2W macros and functions where possible
2018-04-29 IAN LOVES #DEFINES. Overly reworked bit bang base library into defines.
2018-04-30 bitbang base functions for software protocols. I2C updates.
2018-04-30 I2C fix comile warnings and errors
2018-04-30 bitbang library revert to high/low pin functions with direction setup
2018-05-01 - added 2 documents that has the real addresses of the HW register; useful for debugging with commandline gdb - enabled opendrain for HW spi mode
2018-05-07 - added 2 SPI sniffers - added SPI macro's for setting cpol and cpha
2018-05-08 - fixed compile errors introduces by last commit - added I2C sniffer (WIP)
2018-05-09 - added uart macros - added defines for sniffers to platform defines
2018-06-19 - added selftest (~ command)
2018-07-10 - fixed the selftest mode
2018-07-11 add opendrain test to selftest (t to activate after finished selftest)
2018-09-06 comment change in 1wire.c
2018-09-13 Bus Pirate NG1 alpha 3 hardware
2018-12-16 added .gitignore and reference to the blog in the README.md
2018-12-16 removed unnecessary floating point bloat
2018-12-16 re-enable terse build messages
2022-12-28 Add compiling instructions
2022-12-28 Increase cmd buffer size
    This chip has 20KB ram, mostly unused.
    512bytes is ok but we could send much larger payloads.
    Increase buffer size to 16KB, still ~500 bytes free.
2022-12-28 Add more useful documentation
    - Add quick access to pinout
    - Add basic functionality using a Bluepill
2022-12-28 Update README.md
    Little correction
